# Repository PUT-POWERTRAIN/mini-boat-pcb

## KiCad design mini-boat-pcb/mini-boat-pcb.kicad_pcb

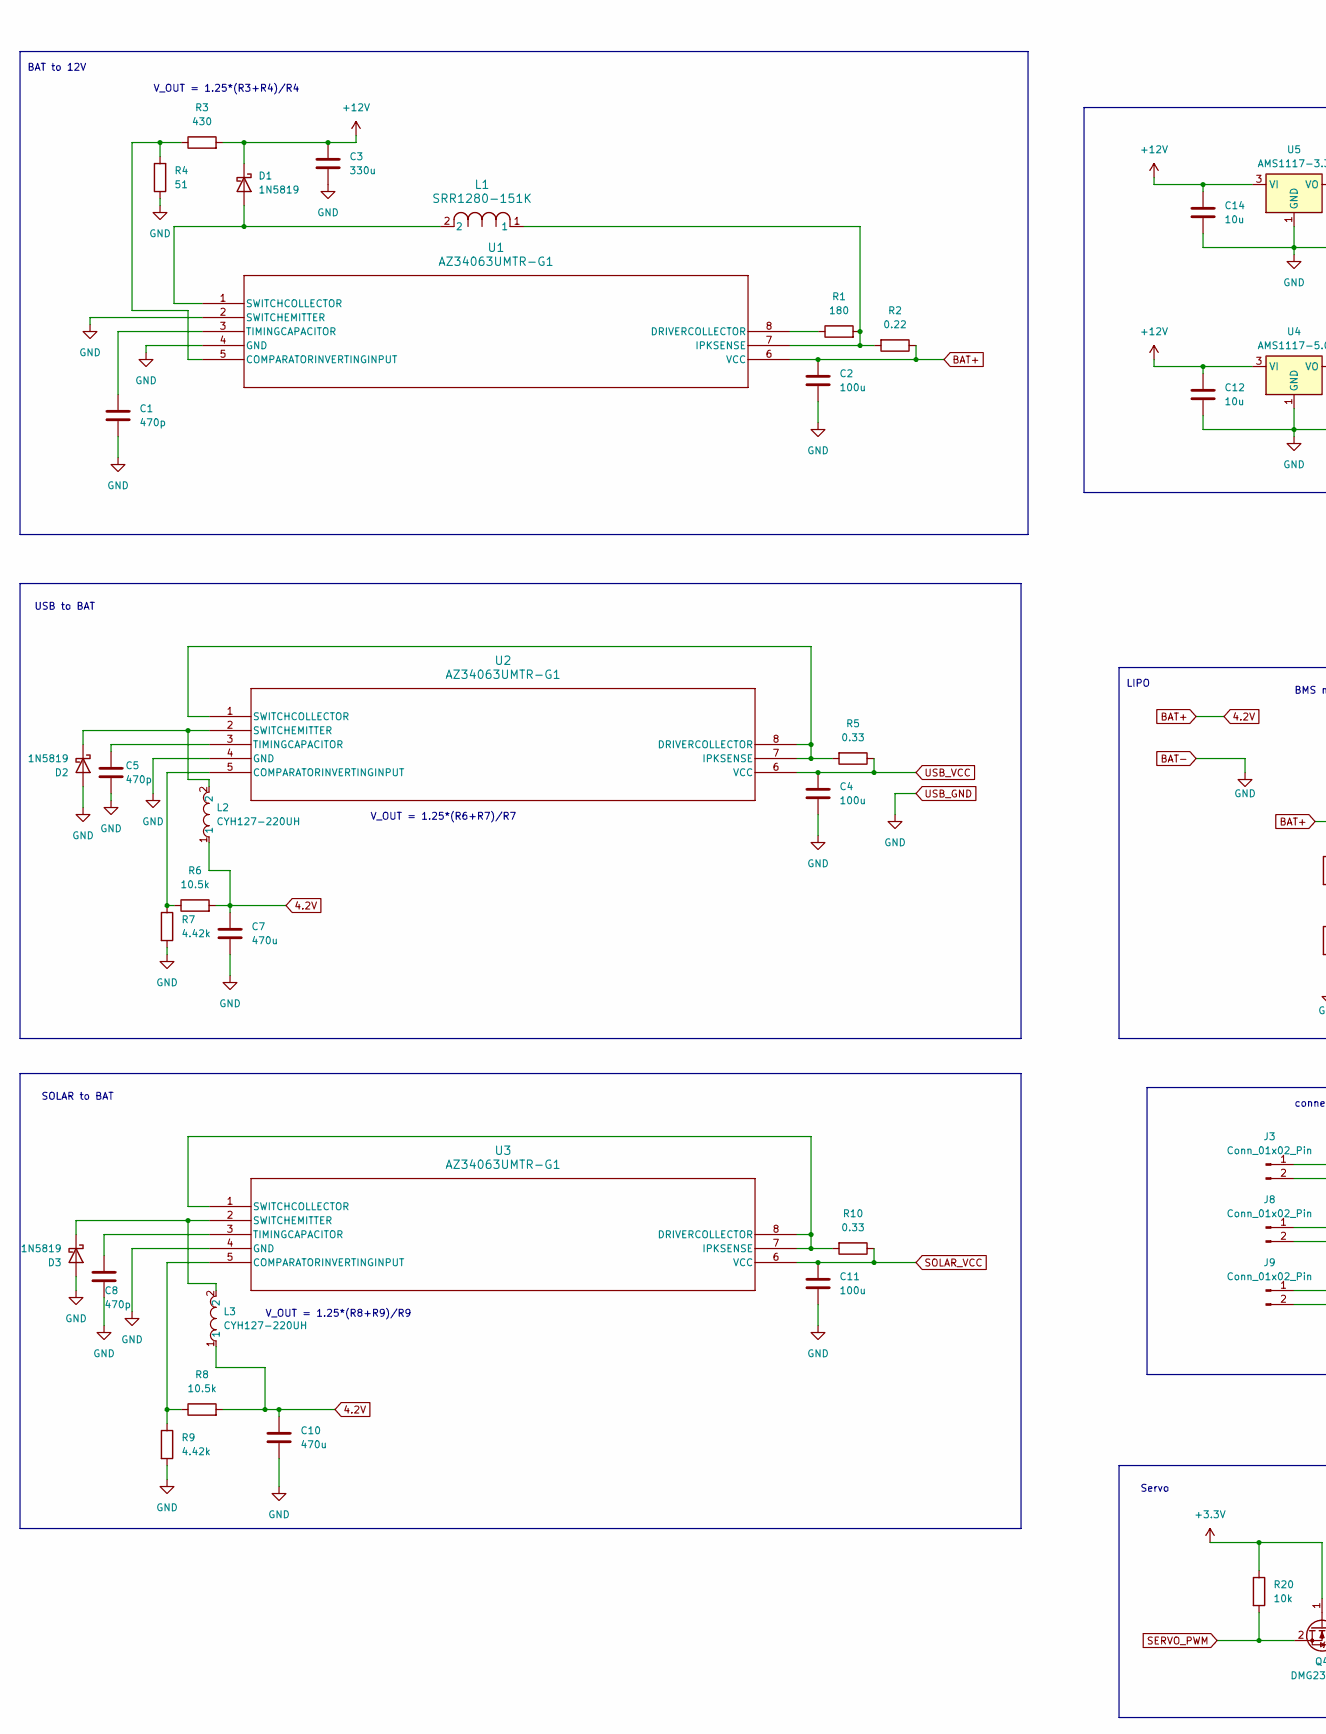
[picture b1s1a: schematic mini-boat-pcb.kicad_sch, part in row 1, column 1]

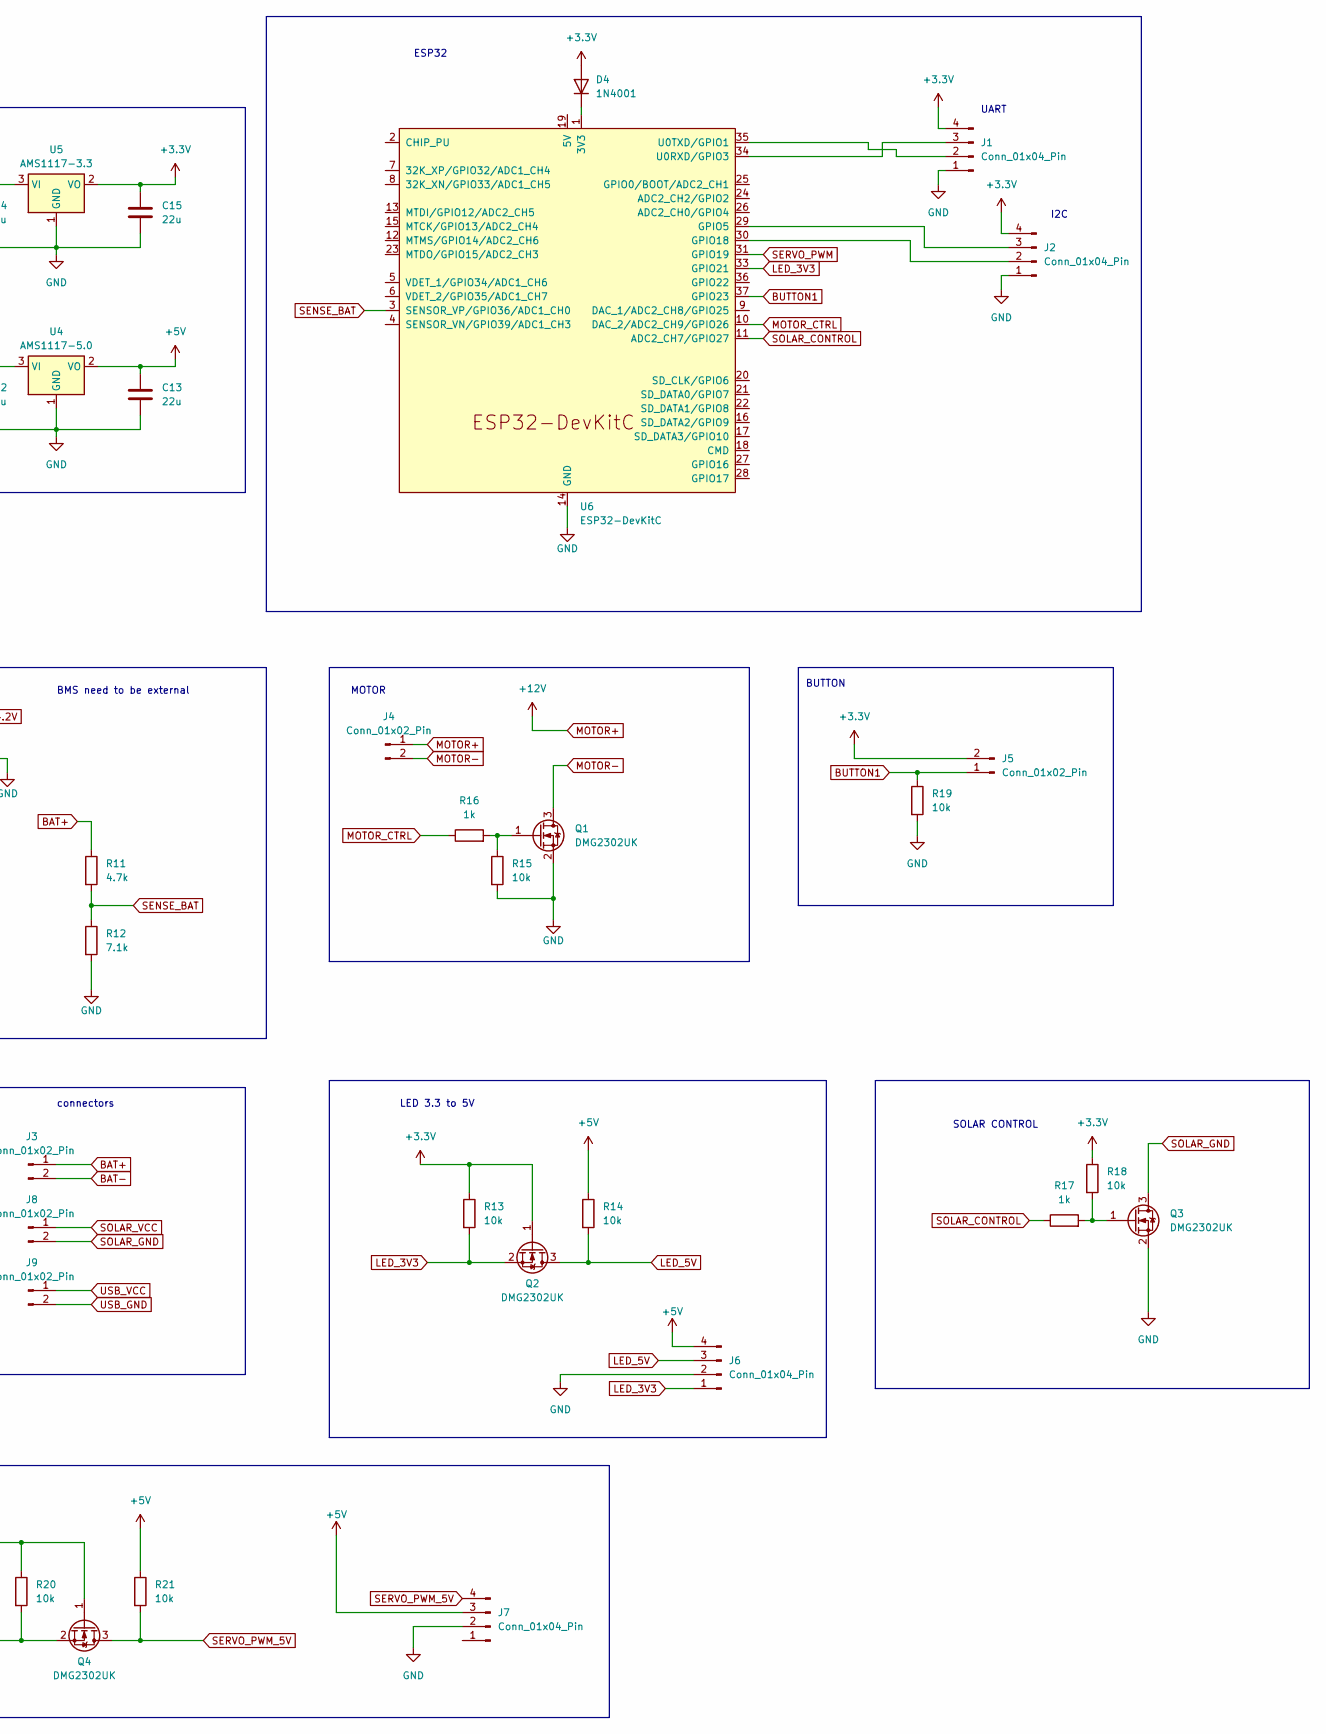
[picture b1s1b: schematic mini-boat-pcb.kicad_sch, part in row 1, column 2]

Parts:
C1, C5, C8: 470p; C_1206_3216Metric_Pad1.33x1.80mm_HandSolder
C2, C4, C11: 100u; C_1206_3216Metric_Pad1.33x1.80mm_HandSolder
C3: 330u; C_1206_3216Metric_Pad1.33x1.80mm_HandSolder
C7, C10: 470u; C_1206_3216Metric_Pad1.33x1.80mm_HandSolder
C12, C14: 10u; C_1206_3216Metric_Pad1.33x1.80mm_HandSolder
C13, C15: 22u; C_1206_3216Metric_Pad1.33x1.80mm_HandSolder
D1, D2, D3: 1N5819; D_DO-41_SOD81_P10.16mm_Horizontal
D4: 1N4001; D_DO-41_SOD81_P10.16mm_Horizontal
J1, J2, J6, J7: Conn_01x04_Pin; PinHeader_1x04_P2.54mm_Vertical
J3, J4, J5, J8, J9: Conn_01x02_Pin; PinHeader_1x02_P2.54mm_Vertical
L1: SRR1280-151K; IND_BOURNS_SRR1280
L2, L3: CYH127-220UH; IND-SMD_L12.3-W12.3; LCSC Part C2929507
Q1, Q2, Q3, Q4: DMG2302UK; TSOT-23_HandSoldering
R1: 180; R_1206_3216Metric_Pad1.30x1.75mm_HandSolder
R2: 0.22; R_1206_3216Metric_Pad1.30x1.75mm_HandSolder
R3: 430; R_1206_3216Metric_Pad1.30x1.75mm_HandSolder
R4: 51; R_1206_3216Metric_Pad1.30x1.75mm_HandSolder
R5, R10: 0.33; R_1206_3216Metric_Pad1.30x1.75mm_HandSolder
R6, R8: 10.5k; R_1206_3216Metric_Pad1.30x1.75mm_HandSolder
R7, R9: 4.42k; R_1206_3216Metric_Pad1.30x1.75mm_HandSolder
R11: 4.7k; R_1206_3216Metric_Pad1.30x1.75mm_HandSolder
R12: 7.1k; R_1206_3216Metric_Pad1.30x1.75mm_HandSolder
R13, R14, R15, R18, R19, R20, R21: 10k; R_1206_3216Metric_Pad1.30x1.75mm_HandSolder
R16, R17: 1k; R_1206_3216Metric_Pad1.30x1.75mm_HandSolder
U1, U2, U3: AZ34063UMTR-G1; SO-8_AZ3406-M_DIO
U4: AMS1117-5.0; SOT-223-3_TabPin2
U5: AMS1117-3.3; SOT-223-3_TabPin2
U6: ESP32-DevKitC

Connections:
4.2V: C2.1, C7.1, C10.1, J3.1, L2.1, L3.1, R2.1, R6.2, R8.2, R11.1, U1.6 (VCC); also elsewhere on the board
+3.3V: C15.1, D4.2 (A), J1.4, J2.4, J5.2, Q2.1 (G), Q4.1 (G), R13.1, R18.1, R20.1, U5.2 (VO)
+5V: C13.1, J6.4, J7.3, R14.1, R21.1, U4.2 (VO)
BAT-: C1.2, C2.2, C3.2, C4.2, C5.2, C7.2, C8.2, C10.2, C11.2, C12.2, C13.2, C14.2, C15.2, D2.2 (A), D3.2 (A), J1.1, J2.1, J3.2, J6.2, J7.2, J9.2, Q1.2 (S), Q3.2 (S), R4.1, R7.2, R9.2, R12.2, R15.2, R19.2, U1.2 (SWITCHEMITTER), U1.4 (GND), U2.4 (GND), U3.4 (GND), U4.1 (GND), U5.1 (GND), U6.14 (GND), U6.32 (GND), U6.38 (GND); also elsewhere on the board
BUTTON1: J5.1, R19.1, U6.37 (GPIO23)
LED_3V3: J6.1, Q2.2 (S), R13.2, U6.33 (GPIO21)
LED_5V: J6.3, Q2.3 (D), R14.2
MOTOR+: C3.1, C12.1, C14.1, D1.1 (K), J4.1, R3.2, U4.3 (VI), U5.3 (VI)
MOTOR-: J4.2, Q1.3 (D)
MOTOR_CTRL: R16.1, U6.10 (DAC_2/ADC2_CH9/GPIO26)
unnamed: D1.2 (A), L1.2, U1.1 (SWITCHCOLLECTOR)
unnamed: D2.1 (K), L2.2, U2.2 (SWITCHEMITTER)
unnamed: D3.1 (K), L3.2, U3.2 (SWITCHEMITTER)
unnamed: D4.1 (K), U6.1 (3V3)
unnamed: J1.2, U6.35 (U0TXD/GPIO1)
unnamed: J1.3, U6.34 (U0RXD/GPIO3)
unnamed: J2.2, U6.30 (GPIO18)
unnamed: J2.3, U6.29 (GPIO5)
unnamed: Q1.1 (G), R15.1, R16.2
unnamed: Q3.1 (G), R17.2, R18.2
unnamed: R3.1, R4.2, U1.5 (COMPARATORINVERTINGINPUT)
unnamed: R1.1, U1.8 (DRIVERCOLLECTOR)
unnamed: L1.1, R1.2, R2.2, U1.7 (IPKSENSE)
unnamed: C1.1, U1.3 (TIMINGCAPACITOR)
unnamed: R6.1, R7.1, U2.5 (COMPARATORINVERTINGINPUT)
unnamed: R5.2, U2.1 (SWITCHCOLLECTOR), U2.7 (IPKSENSE), U2.8 (DRIVERCOLLECTOR)
unnamed: C5.1, U2.3 (TIMINGCAPACITOR)
unnamed: R8.1, R9.1, U3.5 (COMPARATORINVERTINGINPUT)
unnamed: R10.2, U3.1 (SWITCHCOLLECTOR), U3.7 (IPKSENSE), U3.8 (DRIVERCOLLECTOR)
unnamed: C8.1, U3.3 (TIMINGCAPACITOR)
SENSE_BAT: R11.2, R12.1, U6.3 (SENSOR_VP/GPIO36/ADC1_CH0)
SERVO_PWM: Q4.2 (S), R20.2, U6.31 (GPIO19)
SERVO_PWM_5V: J7.4, Q4.3 (D), R21.2
SOLAR_CONTROL: R17.1, U6.11 (ADC2_CH7/GPIO27)
SOLAR_GND: J8.2, Q3.3 (D)
SOLAR_VCC: C11.1, J8.1, R10.1, U3.6 (VCC)
USB_VCC: C4.1, J9.1, R5.1, U2.6 (VCC)

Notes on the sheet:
Servo
UART
BAT to 12V
BMS need to be external
SOLAR to BAT
V_OUT = 1.25*(R8+R9)/R9
BUTTON
LED 3.3 to 5V
SOLAR CONTROL
V_OUT = 1.25*(R6+R7)/R7
ESP32
MOTOR
USB to BAT
I2C
connectors
LIPO
V_OUT = 1.25*(R3+R4)/R4

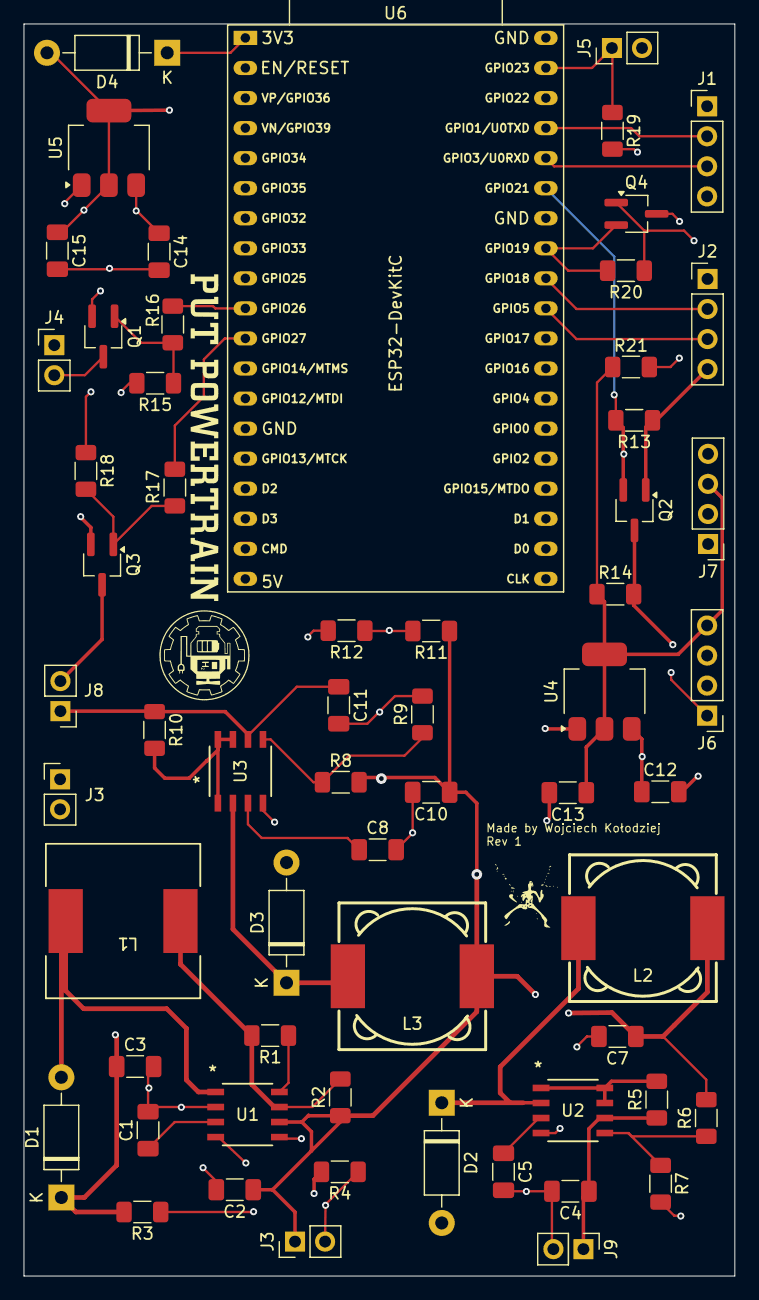
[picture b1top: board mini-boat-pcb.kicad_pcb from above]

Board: 4 copper layers, 60.1 x 105.8 mm, 61 parts (0 on the bottom side), 37 nets.

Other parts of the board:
J3#2: Conn_01x02_Pin; PinHeader_1x02_P2.54mm_Vertical

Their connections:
4.2V: J3#2.1; also elsewhere on the board
BAT-: J3#2.2; also elsewhere on the board

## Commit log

2025-01-06 Upload KiCad files
